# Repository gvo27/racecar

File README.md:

# racecar

This project turns a 1:10 Tamiya TT-02 into a self-driving research platform. It has a two-layer compute stack. A Raspberry Pi 5 does perception, sensor fusion, semantic SLAM and racing-line optimization. An ESP32-S3 does hard-real-time control. This repo holds everything that runs on the car: PWM actuation, failsafes, the host-to-ESP32 protocol, runtime tuning, logging and the Docker/ROS 2 deployment. Setup: [docs/setup.md](docs/setup.md).

## Quick reference

| Task | Commands |
| --- | --- |
| One-time setup (Pi) | `cp .env.example .env`, `make setup`, `make install-host`, `make flash` (ESC off) |
| Start / check / stop | `make car-up`, `make car-ps`, `make car-down` (or `make car-shutdown`) |
| Drive | `make teleop` |
| Sensors | `make viz`, `make rangefinder`, `make lidar-snapshot`, `make lidar-record SECS=30` |
| Tests (no hardware) | `make ros-test`, `make unit`, `make build` |
| Simulation and training | separate repo [racecar-sim](https://github.com/gvo27/racecar-sim). The sim uses the topics in [docs/sensor_contract.md](docs/sensor_contract.md) |
| All targets | `make help` |

**Claude Code plugins.** `.claude/settings.json` lists the project plugins: superpowers, pyright-lsp, clangd-lsp, embedded-skills, ros2-engineering, asd-ste100, claude-md-management, code-simplifier and caveman. Accept the trust prompt, or install each one by hand. Then run `/reload-plugins`:

```bash
claude plugin marketplace add JuliusBrussee/caveman@v4.1.0
claude plugin install <plugin>@<marketplace> --scope project
```

## Compute stack

| Layer | Hardware | Role | Status |
| --- | --- | --- | --- |
| High level | Raspberry Pi 5 | autonomy stack: ROS 2 Jazzy in Docker (`deploy/car/`), supervisor + micro-ROS agent, sends `DriveCmd` (heading, throttle) | phase 2 complete (bench-verified); phase 4 rangefinder + lidar (Slamtec Mapper, `make viz`): compile-only, not bench-verified |
| Real time | ESP32-S3-N16R8 | hardware PWM to servo/ESC, failsafe, telemetry; micro-ROS client over UART0 | this repo, `firmware/esp32/` (env `esp32s3`, micro-ROS) |

## Current inventory

| Component | Item | Documentation |
| --- | --- | --- |
| chassis | Tamiya TT-02 | — |
| battery | 2S 7.4V 80C 5200mAh LiPo Battery Pack | — |
| microcontroller | ESP32 S3 N16R8 | [user guide](https://github.com/microrobotics/ESP32-S3-N16R8/blob/main/ESP32-S3-N16R8_User_Guide.pdf) |
| edge compute | Raspberry Pi 5 | 5V 5A |
| voltage regulator for compute rail | Pololu D36V50F5 (5V 5.5A, 6-50V in) | [pololu.com/product/4091](https://www.pololu.com/product/4091), [archived](docs/datasheets/Pololu%20-%205V%2C%205.5A%20Step-Down%20Voltage%20Regulator%20D36V50F5.htm) |
| rangefinder | Garmin LIDAR-Lite v4 LED, part number 010-02022-00 | [archived PDF](docs/datasheets/LIDAR-Lite%20LED%20v4%20Instructions_EN-US.pdf), [summary](docs/datasheets/rangefinder_lidar_lite_v4.md), [instructions](https://static.garmin.com/pumac/LIDAR-Lite%20LED%20v4%20Instructions_EN-US.pdf) (software name: rangefinder) |
| lidar | Slamtec Mapper M2M1 | [datasheet digest](docs/datasheets/slamtec_mapper_M2M1_datasheet.md) |
| motor controller | THW-1060-BRUSHED | [thw-1060-brushed-esc.md](docs/datasheets/thw-1060-brushed-esc.md) |
| steering servo | DS3225MG | [ds3225_servo.md](docs/datasheets/ds3225_servo.md) |

## Microcontroller Pin map (left header P1 only)

Source of truth: [`firmware/esp32/include/pins.h`](firmware/esp32/include/pins.h). Keep this table identical to it.

```
                ESP32-S3-N16R8   (top view, antenna up)
          P1 (LEFT header)
        ┌─────┬──────────────────────────────┐
  3V3   │  1  │ unused (sensors: own rail)   │
  3V3   │  2  │ unused                       │
  RST   │  3  │ ✗ do not use                 │
  GPIO4 │  4  │ ● STEER_PWM   → servo signal │
  GPIO5 │  5  │ ● THROTTLE_PWM→ ESC signal   │
  GPIO6 │  6  │ ○ BATT_LOW                   │
  GPIO7 │  7  │ ○ IMU_INT                    │
  GPIO15│  8  │ ○ ENC_A                      │
  GPIO16│  9  │ ○ ENC_B                      │
  GPIO17│ 10  │ · spare (UART1 TX)           │
  GPIO18│ 11  │ · spare (UART1 RX)           │
  GPIO8 │ 12  │ ● I2C SDA → rangefinder 3    │
  GPIO3 │ 13  │ ✗ strapping                  │
  GPIO46│ 14  │ ✗ strapping                  │
  GPIO9 │ 15  │ ● I2C SCL → rangefinder 4    │
  GPIO10│ 16  │ · spare                      │
  GPIO11│ 17  │ · spare                      │
  GPIO12│ 18  │ · spare                      │
  GPIO13│ 19  │ · spare                      │
  GPIO14│ 20  │ · spare                      │
  5V    │ 21  │ input only - leave unwired   │
  G     │ 22  │ ■ COMMON GROUND (ESC/servo)  │
        └─────┴──────────────────────────────┘
          [USB] left        [COM] right ← flash / host
   ● active   ○ reserved (no code yet)   · spare   ✗ do not use   ■ ground
```

| P1 # | GPIO | Function | Status |
| --- | --- | --- | --- |
| 4 | 4 | **STEER_PWM** → DS3225 signal | **active** |
| 5 | 5 | **THROTTLE_PWM** → ESC signal | **active** |
| 6 | 6 | *BATT_LOW* (hi/low input) | *reserved* |
| 7 | 7 | *IMU_INT* | *reserved* |
| 8 / 9 | 15 / 16 | *ENC_A / ENC_B* (shaft encoder) | *reserved* |
| 12 / 15 | 8 / 9 | **I2C SDA / SCL** → rangefinder (Garmin pin 3 / 4) | **active** |
| 10, 11, 16-20 | 17, 18, 10, 11, 12-14 | spare | spare |
| 3, 13, 14 | RST, 3, 46 | ~~reset / strapping pins~~ | ~~do not use~~ |
| 22 | G | common ground | power |

Wire colours: signal = yellow/white, power = red, ground = black. Rangefinder I2C: SDA = white, SCL = green. Put a tape flag on the two active signal wires.

## Make commands

This section lists day-to-day commands only, in the order you use them. `make help` lists everything (dev, CI and firmware tools too). [docs/setup.md](docs/setup.md) has the details.

**Once per Pi.** First, run `cp .env.example .env` and add yourself to the `docker` and `dialout` groups (docs/setup.md §1).

| # | Command | What it does |
| --- | --- | --- |
| 1 | `make setup` | Checks git, make and docker. Builds both Docker images (it runs `fw-image` and `ros-image`) |
| 2 | `make install-host` | Needs sudo. Names the ESP32 `/dev/rccar-esp32` and starts the car stack at every boot. Afterwards, unplug the USB cable and plug it in again one time |
| 3 | `make flash` | Switch the ESC off first. Uploads the firmware to the ESP32. Run it again only when `firmware/` changes |

You do not need to run `make config` by hand. `car-up` and the boot service run it.

**Every session**

| # | Command | What it does |
| --- | --- | --- |
| 1 | `make car-up` | Starts the stack (micro-ROS agent, supervisor, lidar driver). After a boot it already runs if you did `install-host`. Running it again is harmless |
| 2 | `make car-ps` | Wait until every service shows `healthy`. Then switch the ESC on |
| 3 | `make teleop` | Drives the car over SSH (arrows, space = brake, `x` = disarm + quit) |
| 4 | `make car-shutdown` | Disarms, stops the stack and offers to power off the Pi. Then switch the ESC off |

**Sensors** (stack running)

| Command | Sensor | What it does |
| --- | --- | --- |
| `make rangefinder` | rangefinder (Garmin LIDAR-Lite v4) | Shows a live distance feed in the terminal |
| `make viz` | lidar (Slamtec Mapper) | Shows scan, map and pose on `localhost:8765` for Foxglove. Forward the port with VS Code SSH |
| `make lidar-imu` | lidar (Slamtec Mapper) | Shows live heading, yaw rate, speed and acceleration. Also saves them to `logs/` |
| `make lidar-snapshot` | lidar (Slamtec Mapper) | Makes one capture to `logs/`: `map.png` (map + scan + pose) and a text summary. Claude Code can read both |
| `make lidar-record SECS=30` | lidar (Slamtec Mapper) | Records the lidar topics to a rosbag (`.mcap`, opens in Foxglove) in `logs/` |
| `make lidar-hw-test` | lidar (Slamtec Mapper) | Automated PASS/FAIL check of the real unit with the car still. Run `make drivers-stop` first and `make car-up` afterwards |

**When needed**

| Situation | Commands |
| --- | --- |
| something looks wrong | `make car-logs` |
| USB cable replugged | `make car-down`, then `make car-up` |
| first drive, or the servo/linkage changed | `make calibrate`, then `make test` (steering sweep; the motor never runs) |
| edited `tuning.toml` | `make tune` |
| after `git pull` | `make car-down`, `make ros-image`, `make flash` (only if `firmware/` changed, ESC off), `make car-up` |

## Wiring: Rangefinder (Garmin LIDAR-Lite v4 LED)

The software name is *rangefinder*. Datasheet: [archived PDF](docs/datasheets/LIDAR-Lite%20LED%20v4%20Instructions_EN-US.pdf), [summary](docs/datasheets/rangefinder_lidar_lite_v4.md). Power off while wiring.

| Garmin pin | Name | Wire | Connect to |
| --- | --- | --- | --- |
| 1 | VIN (5 V, 4.75-5.25 V) | red | regulated 5 V **sensor rail** (never ESP32 5V/3V3) |
| 2 | GND | black | common ground (P1-22) |
| 3 | I2C SDA | **white** | GPIO8 (P1-12) |
| 4 | I2C SCL | **green** | GPIO9 (P1-15) |
| 5-10 | GPIOA, GPIOB, nRF debug | n/a | leave unconnected |

## Power rules

1. **The ESP32 powers nothing.** It outputs only actuator signals and communications. A separate regulated power rail powers the sensors. This rail shares ground with the ESP32. All signals stay at ≤ 3.3 V.
2. Servo power comes from the built-in 6 V / 3 A BEC of the ESC (red wire of the throttle lead). Connect it with a Y-harness.
3. Connect the grounds of the ESP32, ESC and servo (P1-22).

## Power-up sequence

1. ESC **off**. Wheels off the ground.
2. Connect the USB cable to **COM**. The ESP32 boots and sends neutral (1500 µs) on both channels. Then run `make car-up`.
3. ESC **on**. It beeps and learns neutral.
4. To power down, do the steps in reverse order. Switch the ESC off first. **Always switch the ESC off before `make flash`.**

## Repo layout

```
rccar_msgs/        interface contract: DriveCmd, Telemetry, McuEvent, SupervisorState, McuCommand, Reset, ...
rccar_supervisor/  safety authority: arbitration, latched stop, sole publisher of /rccar/mcu/drive
rccar_mcu_bridge/  lifecycle node: typed services over McuCommand, tuning push, FIRMWARE_KEYS
rccar_teleop/      admin keyboard teleop (SSH)
rccar_calibration/ calibrate, bench_test, tune
rccar_bringup/     launch (car.launch.py), tuning.toml -> ROS parameters
firmware/esp32/    ESP32 firmware (PlatformIO): src/main.cpp, include/pins.h, extra_packages/rccar_msgs (synced copy), rccar.meta
deploy/car/        compose.yaml, 99-rccar.rules (udev), rccar.service (systemd); deploy/render_env.py (make config)
docker/            firmware.Dockerfile, ros.Dockerfile (+ entrypoint.sh, ros-test.sh)
models/            manifest.yaml (weights are not in git), cache/ gitignored
repos/             rccar.repos (third-party ROS sources, vcstool)
tuning.toml        all runtime tuning + [platform.*]; pushed to the ESP32 by mcu_bridge
.env.example       template for the gitignored .env
logs/              session history (*.jsonl, gitignored)
docs/              setup.md, docker_ros_plan.md, proposal, datasheets/
.claude/           CLAUDE.md, layout.yaml, rules/, agents/
.github/           workflows/{firmware,ros}.yml
Makefile           every command (make help)
```

Bench checklist (the procedure that verified phase 2): [docs/setup.md](docs/setup.md#phase-2-bench-checklist-user-run). Roadmap: [docs/docker_ros_plan.md](docs/docker_ros_plan.md). Firmware design: [docs/esp32-firmware-proposal.md](docs/esp32-firmware-proposal.md).

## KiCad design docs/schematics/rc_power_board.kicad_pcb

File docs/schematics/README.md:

# Power distribution board (baseline schematic)

Draft KiCad project for the car's power board. A 2S LiPo comes in; the board puts out `VBAT`, `+5V_CPU`, `+5V_SENS` and `+3V3_SENS` on a common `GND`, and routes `+6V_BEC` from the ESC to the servo. The ESC's own battery power is off-board. This is a **review draft**: every value marked `TBD` is unconfirmed (project rule: no unconfirmed parameters).

| File | What it is |
| --- | --- |
| `design_overview.md` | The design meeting summary: one short entry per feature, the power budget and the decisions wanted. |
| `bom.md` | How the BOM is made (`make bom`, symbol fields), fuse notes, stock notes. |
| `bom.csv` | BOM exported from the schematic fields by `make bom` (generated; commit it). |
| `bom_offboard.csv` | Hand-kept BOM of parts with no symbol (XH housings, crimps, stock, J6/J7 options). |
| `fab_handoff.md` | Rev A CNC-milling handoff (Makera Carvera) plus later-revision fab checklist: DRC/net classes, rivets, holes, IPC-2221 table, connector table, export, sign-off. |
| `power_board_plan.md` | The build guide and background: rails, power budget, trace widths, a step-by-step KiCad guide and open questions. Exported from the live doc linked at its top. |
| `power_architecture.png` | Block diagram used by the plan. |
| `rc_power_board.kicad_pro` / `.kicad_sch` | KiCad project and the one-sheet A3 schematic (regions A to E plus notes). |
| `rc_power.kicad_sym` + `sym-lib-table` | Project symbol library: `D36V50F5` (all 12 module pins, used by U1 and U2), `REG_MODULE` (generic VIN/GND/VOUT/EN, no longer used on the board) and one power symbol per rail. |
| `rc_power_board.kicad_pcb` / `.kicad_dru` | Rev A board, routed, for review only (no Gerber or CAM files). The `.kicad_dru` holds rule `U3_fine`. |
| `rc_power.pretty/` + `fp-lib-table` | Project footprint library: `Pololu_D36V50Fx` (U1 and U2: 12 pads and the full 25.4 x 25.4 mm body, from Pololu's drawing; facts in `docs/datasheets/regulator_pololu_d36v50f5.md`). |
| `milling.toml`, `milling_waivers.toml` | Milling limits (each value `assumed` or `confirmed`) and the waiver list for the milling check. |
| `tools/` | Python tools and tests that run in the KiCad image: `build_pcb.py`, `placement.py`, `route_pcb.py`, `check_board.py`, `milling_check.py`, `review_plots.py`. |
| `review/` | Review package: DRC report, milling check, layer PDF, 1:1 PDF, `README.md`. |
| `rc_power_board.pdf` | Plot of the sheet, for review without KiCad. |
| `.kicad-happy.json` | Config for the kicad-happy Claude plugin (analysis output in `analysis/`, gitignored except the manifest). |

## KiCad version

The project version is **KiCad 10.0**; KiCad 9 or older cannot open a KiCad 10 save.

The committed `.kicad_sch` is now KiCad 10 format: `kicad-cli sch upgrade` (10.0.8) saved it with the U2 footprint change. The owner's GUI steps stay open: Update Symbols from Library (the 3 `lib_symbol_mismatch` warnings, D2 to D4), a re-plot of the PDF, and the owner's KiCad 10 ERC.

The single-fuse revision is regenerated in KiCad 7 format again. Owner steps: close KiCad, pull, open, Update Symbols from Library, save, run ERC, re-plot the PDF, push.

Previous revision: the meeting-cleanup revision was generated in KiCad 7 format, then opened, symbol-updated (D2–D4) and saved in KiCad 10.0 by the owner (94ccd72), with label positions tidied in dd946f3. Edit the KiCad 10 files from here on; close KiCad before pulling. `rc_power_board.kicad_pro` (net classes, ERC severities) is the owner's KiCad 10 file.

## U1 and U2 = Pololu D36V50F5 (current revision)

- **U1 and U2** are both the Pololu D36V50F5 (#4091, 5 V, 5.5 A typical). Owner decision 2026-11-12: the owner has two modules, and the same part on both rails gives a swap spare. This replaces the D24V90F5 assumption for U2 (2026-11-11).
- Facts, archived drawing and graphs: `docs/datasheets/regulator_pololu_d36v50f5.md`. The D24V90F5 note stays as history (`regulator_pololu_d24v90f5.md`, superseded).
- Both modules use the symbol `rc_power:D36V50F5` and the footprint `rc_power:Pololu_D36V50Fx`. The footprint shows the real 25.4 x 25.4 mm body (the first rev A layout used a plain pin header and put the body over J6 and J7). U2 EN, VRP and PG have no-connect flags, as U1 EN and VRP.
- **Flag:** dropout is about 1.0 V at 5 A (Pololu graph). Near the 6.0 V cutoff the +5V_SENS output can fall below 5 V, and the Mapper needs at least 4.8 V. Bench check at J11 during Mapper startup.
- Decisions on 2026-11-11 (owner): no reverse-polarity protection on rev A (the modules have their own); U3 keeps the stock SOT-23-5 footprint with the `U3_fine` DRC rule.
- Plan: `docs/plans/2026-11-11-power-board-pcb-rev-a.md` (Task 7c).

## Rev A PCB (review only)

The board is built and routed headless in the pinned KiCad 10.0.8 image: `make kicad-image`, then `make erc pcb-build pcb-route pcb-check pcb-mill-check pcb-review pcb-test`. Freerouting 2.5.0 (pinned by digest) routes it. `pcb-build` refuses to overwrite an existing board without `--force`: after the first build the `.kicad_pcb` is the owner's file. Results, assumptions and the owner's GUI checks are in `review/README.md`. Gerber, drill and CAM export wait for the lab tech.

## ATO fuse, JST-XH convention, Garmin I2C (earlier revision)

- **F1** is a standard ATO/ATC blade fuse in a Littelfuse FLR 178.6165.0001 holder (`Fuse:FuseHolder_Blade_ATO_Littelfuse_FLR_178.6165`); value `TBD ATO/ATC blade 15A` (15 A decided by the Mapper load, see the Mapper revision below). Proposed fuse: Littelfuse 0257015.PXPV (15 A). Details in `bom.md`.
- **JST-XH (2.5 mm) is the connector convention** for sensors and low-power parts (single Dupont jumper sockets push onto the XH pins for breadboard debugging; 2.54 mm multi-pin housings do not fit; parts in lab stock). Exceptions: J1 (battery T-plug pads), J6/J7 (USB-C pigtail screw terminals, over 3 A).
- **J3, J4:** 3-pin XH, pins 1 GND, 2 +6V_BEC, 3 signal (follows the ESC/servo lead; XH 2.50 mm does not mate with stock 2.54 mm plugs: re-terminate only 22 AWG leads, else an adapter lead). **J5:** 6-pin XH: 1 `U1_PG` (GPIO TBD), 2 `THROTTLE_PWM` GPIO5, 3 `STEER_PWM` GPIO4, 4 `I2C_SDA` GPIO8, 5 `I2C_SCL` GPIO9, 6 GND. **J8:** Garmin LIDAR-Lite v4, 4-pin XH, pin order = Garmin 1-4 (+5V_SENS, GND, SDA, SCL); no external I2C pull-ups. J9, J11-J14 stay 2-pin XH (1 V+, 2 GND); J11 now hosts the Slamtec Mapper (see below). Pin order convention and crimp table: `fab_handoff.md`.
- **Netlist then: 39 parts, 21 nets** (adds `I2C_SDA`, `I2C_SCL`); now 40 parts, 21 nets (see the Mapper revision).
- **Power5A** track width is 1.6 mm (now also `+5V_SENS`, see below). Computed IPC-2221 widths are in `fab_handoff.md` (2 oz stock).
- **Owner steps:** close KiCad, pull, open, Update Symbols from Library, save in KiCad 10, run ERC, Assign Footprints check (XH and ATO footprints), re-plot the PDF, push.

## Slamtec Mapper on `+5V_SENS` (earlier revision)

- **J11** (was `Spare 5V`) now hosts the Slamtec Mapper M2M1 lidar. Harness: J11 2-pin XH, XHP-2 housing, 22 AWG 3 A USB-A male 2-wire pigtail (pin 1 `+5V_SENS` to red/VBUS, pin 2 GND to black). Mapper supply 4.8 V min / 5 V typ / 12 V max; running 0.75 A typ, 1.3 A max; startup 1.4-1.6 A for a few seconds; ripple 20 mV typ, 50 mV max (from its datasheet on branch `lidar`). Not powered from Pi USB or straight from the pack.
- **C9** (`Device:C_Polarized`, `TBD >=100uF low-ESR >=10V`, footprint `CP_Radial_D8.0mm_P3.50mm`) added on `+5V_SENS` / GND at J11 for the startup surge and ripple.
- **Budget (computed):** `+5V_SENS` 3.3 A -> 4.6 A worst case running, 4.9 A at Mapper startup. U2 must now be >= 6 A: the Pololu D36V50F5 (owner 2026-11-12) gives about 7.4 A at 6 V in and about 8 A at 8.4 V in (Pololu graph); dropout near the 6.0 V cutoff is a bench check. U2 input 3.99 A at 6.4 V, 4.26 A at 6.0 V; U1 input 4.43 A / 4.72 A. Board `VBAT` load about 8.4 A at 6.4 V, 9.0 A at 6.0 V, about 9.3 A briefly at startup (was 7.3 / 7.8 A).
- **F1 = 15 A** (10 A would run at 84-93 % of rating, over the ~75 % rule; 15 A gives 56-62 %). Copper stays sized for 16.5 A. Inrush margin unchanged.
- **Net classes:** `+5V_SENS` moved from Power3A (1.0 mm) to Power5A (1.6 mm) in `rc_power_board.kicad_pro` (about 4.9 A; IPC-2221 5.0 A row, 2 oz: 1.4 mm at ΔT 10 C). `*+6V_BEC` stays Power3A.
- **DRC rules** in `rc_power_board.kicad_pro` (board.design_settings.rules) set to match the CNC docs: `min_clearance` 0.4, `min_track_width` 0.5, `min_via_diameter` 2.0, `min_via_annular_width` 0.45, `min_through_hole_diameter` 0.8 (C9 drill; methods TBD).
- **Schematic:** J3 and its wires/symbols sit 1.27 mm up-left of the generator's old position, ported from the owner's 53ac275 save. Netlist: 40 parts, 21 nets; everything but C9 is identical to the previous revision. Notes box updated (budget, F1, U2, `+5V_SENS` class, new note 14 for the Mapper).
- **Owner steps:** open in KiCad 10, Update Symbols, save, run ERC, re-plot; choose C9 and U2 parts.

## CNC-milled prototype (Makera Carvera)

Rev A is milled in-house from Kepro P22-465G 2 oz double-sided FR-4 (4" x 6", 152.4 x 101.6 mm; lab template, `example/README.md`); no fab house, no plated holes, vias are soldered copper rivets.

- **Rivets (update):** lab stock is an LPKF EasyContac kit (0.6/0.8/1.0/1.2 mm, with setting tool). Default via = 0.8 mm rivet, drill 1.1 mm, pad 2.0 mm (matches the existing `.kicad_pro` via settings); 1.2 mm optional for high current. Table and source: `fab_handoff.md`. BOM rivets now $0.

- **`rc_power_board.kicad_pro`:** all four net classes clearance 0.2 -> 0.4 mm; Default track 0.25 -> 0.5 mm; via diameter/drill for all classes -> 2.0 / 1.1 mm (LPKF EasyContac 0.8 mm rivet). DRC rules set: clearance 0.4, track 0.5, via 2.0/1.1, annular 0.45, min hole 0.8; plan's net-class table updated.
- **Docs:** `fab_handoff.md` restructured (A: CNC prototype, B: fab house later) with a JST header table for every external connection; `bom.md` adds stock, rivets, dowels, bits and optional VH/XH rows, no PCB fab cost (total about 87.0 USD, about 47.1 excluding U1 after the rivet update); `design_overview.md` and `.claude/rules/schematics.md` updated.
- **Owner steps:** pull; open Board Setup in KiCad 10 and verify the preloaded design-rule minimums (clearance 0.4, track 0.5, via 2.0, annular 0.45, min hole 0.8); the net-class values are provisional; confirm the bit list (incl. a 1.1 mm bit) with the lab tech; decide the U3 footprint option. (The DRC minimums are now set in `rc_power_board.kicad_pro`, see the Mapper revision; the Mapper question is decided.)

## Meeting-cleanup revision (what changed)

- **Wiring for traceability.** Each region's local nets (`VBAT_RAW`, `LDO_IN`, the rail outputs; `VIN_CPU`/`VIN_SENS` were merged into `VBAT`, see below) run as one bus from source to load, with no crossings. Each bus carries a single net label so the net keeps its name. GND is still drawn as symbols.
- **ESC power is off-board.** The battery feeds the ESC directly on its own 12 AWG leads, carrying up to 20 A of motor current. J2, F2 and `VBAT_ESC` are removed. On the board, the ESC is now only the J3 3-wire receiver lead: throttle PWM plus the 6 V BEC. Board load on `VBAT` was then about 7.3 A worst case (about 7.8 A at the 6.0 V cutoff; now 8.4 / 9.0 A with the Mapper, F1 = 15 A). A note on the sheet records the ESC draw.
- **U1 EN is left unconnected (feature archived).** The module's internal pull-up keeps U1 always on. Q1, R4, `ESP_SHDN` and region F are removed. U1 PG still goes to the ESP32.
- **The radar header (J10) is removed.** The gap in reference numbers is deliberate, so J11 keeps its name.
- **`+6V_BEC`** now uses a project rail symbol, like the other rails.
- **J5** was 4-pin in this revision (now 6-pin, see the current revision): 1 `U1_PG`, 2 `THROTTLE_PWM` (GPIO5), 3 `STEER_PWM` (GPIO4), 4 GND. The `U1_PG` GPIO is TBD until firmware adds it; when it does, update `pins.h` and the README pin table together.

## Single-fuse revision (what changed)

- **One replaceable main fuse, F1, for the whole board** (compute and both sensor rails), because the fuse inventory is high-current. Branch fuses F3 (compute) and F4 (sensor) are removed.
- **Nets `VIN_CPU` and `VIN_SENS` are gone**, merged into `VBAT` (class HighCurrent). U1 VIN and U2 VIN sit directly on `VBAT`.
- **F1** was a Mini (ATM) blade fuse in a Keystone 3568 holder (superseded by the ATO/ATC revision above). Rating discussion is in `bom.md`.
- **Trade-off:** a sensor-branch short now opens F1 and drops compute too. U1 and U2 have their own output current limiting.
- **Netlist then: 39 parts, 19 nets (now 40 parts, 21 nets, see the Mapper revision).** Net classes then: HighCurrent = `*VBAT*`, GND; Power5A = `+5V_CPU`; Power3A = `+5V_SENS`, `*+6V_BEC` (now `+5V_SENS` is Power5A).
- **U1 EN** stays unconnected until the rev 2 prototype board. U1 is in hand; U2 is not bought yet.
- **New docs:** `bom.md` and `fab_handoff.md`.

## Design notes

- **Rail symbols.** Each rail is a project power symbol whose hidden pin name and Value both equal the rail name, instead of a renamed `power:VCC`. This keeps nets correct in KiCad 7 (where the pin name sets the net) and in 8 and later (where the Value does).
- **U1, Pololu D36V50F5.**
  - Drawn with all 12 pins: 1 PG, 2 EN, 3–4 VRP, 5–6 VIN, 7–10 GND, 11–12 VOUT.
  - Footprint `PinHeader_2x06_P2.54mm_Vertical`. Check the pin numbering against Pololu's dimension drawing before layout.
  - Each header pin is rated 3 A, so VIN, VOUT and GND use their pin pairs.
  - VRP is unused: the sensor buck is fed from `VBAT` (VRP would overload U1's 6 A VIN pin pair).
  - Rated 5.0 V / 5.5 A, against the plan's 5.1 V / ≥ 6 A target.
- **J1** is a pair of wire pads for the battery's T-plug pigtail (12 AWG). The pad footprint is a placeholder; size TBD.
- **J6/J7** are 2-wire USB-C pigtails into the Pi 5 and the ESP32's left USB-C port, so each board's own USB-C input protection stays in the path. They are 20 AWG, 30 cm long, and drop about 0.10 V at 5 A; trim them to 10–15 cm.
- **PWR_FLAG** symbols are ERC-only markers. They tell ERC that power enters a net that is fed through a fuse or ferrite. They have no physical part and are not on the PCB. The probe points are TP1–TP3.
- **LED resistors** connect pin-to-pin to their LEDs, so those three nets carry KiCad's auto names (`Net-(D2-A)` and so on).
- **Net-class patterns** are `*VBAT*`, `+5V_CPU`, `+5V_SENS` and `*+6V_BEC`. The leading `*` matches the `/` that KiCad puts in front of local-label nets.
- **D1** is `Device:D_Zener`, used as a unidirectional TVS, cathode to `VBAT`.
- **Placeholder footprints.** All ratings are TBD; pick real parts before layout.
  - F1: `Fuse:FuseHolder_Blade_ATO_Littelfuse_FLR_178.6165` (ATO/ATC blade).
  - C1: 10 mm radial electrolytic.
  - D1: SMB.
  - FB1: 0805.
  - TP1–TP3: 1.5 mm pads.
  - U2: module TBD, no footprint yet.

## Verification so far

The current revision (Mapper on J11): **40 parts, 21 nets**, per the regenerated netlist (KiCad 7.0.11 `kicad-cli`); the only netlist change vs the previous revision is C9 added to `+5V_SENS` / GND. The kicad-happy analyzer finds 40 parts, 21 nets, 4 no-connects and the same findings as before. The owner's KiCad 10 ERC on this revision is pending (the previous save, 53ac275, was clean). The figures below are from the earlier (41 parts, 21 nets) revision.

The previous revision was checked with KiCad 7.0.11 `kicad-cli`, the kicad-happy analyzer and the owner's KiCad 10 ERC:

- **Netlist: 41 parts, 21 nets.** The only single-pin nets are U1 EN, U1 VRP ×2, U2 EN and U3 NC. All of them are intentionally unconnected and carry no-connect flags.
- **Analyzer:** finds the same 41 parts and 21 nets. U1 and U2 are classified as switching regulators, U3 as a 3.3 V LDO, and D2–D4 as resistor-limited LEDs. The remaining findings are expected for a draft:
  - no MPNs or datasheets (all TBD);
  - no footprint for U2;
  - "missing pull-up" on U1 PG (the ESP32's internal pull-up handles it);
  - "missing pull-up" on U3 EN (it is tied to VIN, per the AP2112 datasheet).
- **PDF:** rendered and visually checked: no wire crossings in any region, and no text overlaps.
- **ERC in KiCad 10 (owner-run, 94ccd72): clean**, after Update Symbols from Library. `rc_power_board.pdf` re-plotted from KiCad 10 (dd946f3).
- **Analyzer on the KiCad 10 save (dd946f3):** still 41 parts, 21 nets, 4 no-connects, so the upgrade and label tidy changed no connections.
- **Not yet done:** SPICE, PCB layout.

## Working on this folder with Claude Code

The repo enables the kicad-happy plugin (`.claude/settings.json`). Rules for this folder are in `.claude/rules/schematics.md`. Typical asks are "review docs/schematics", "check the power budget against the schematic" and "simulate the subcircuits". SPICE needs `ngspice` installed on the host.

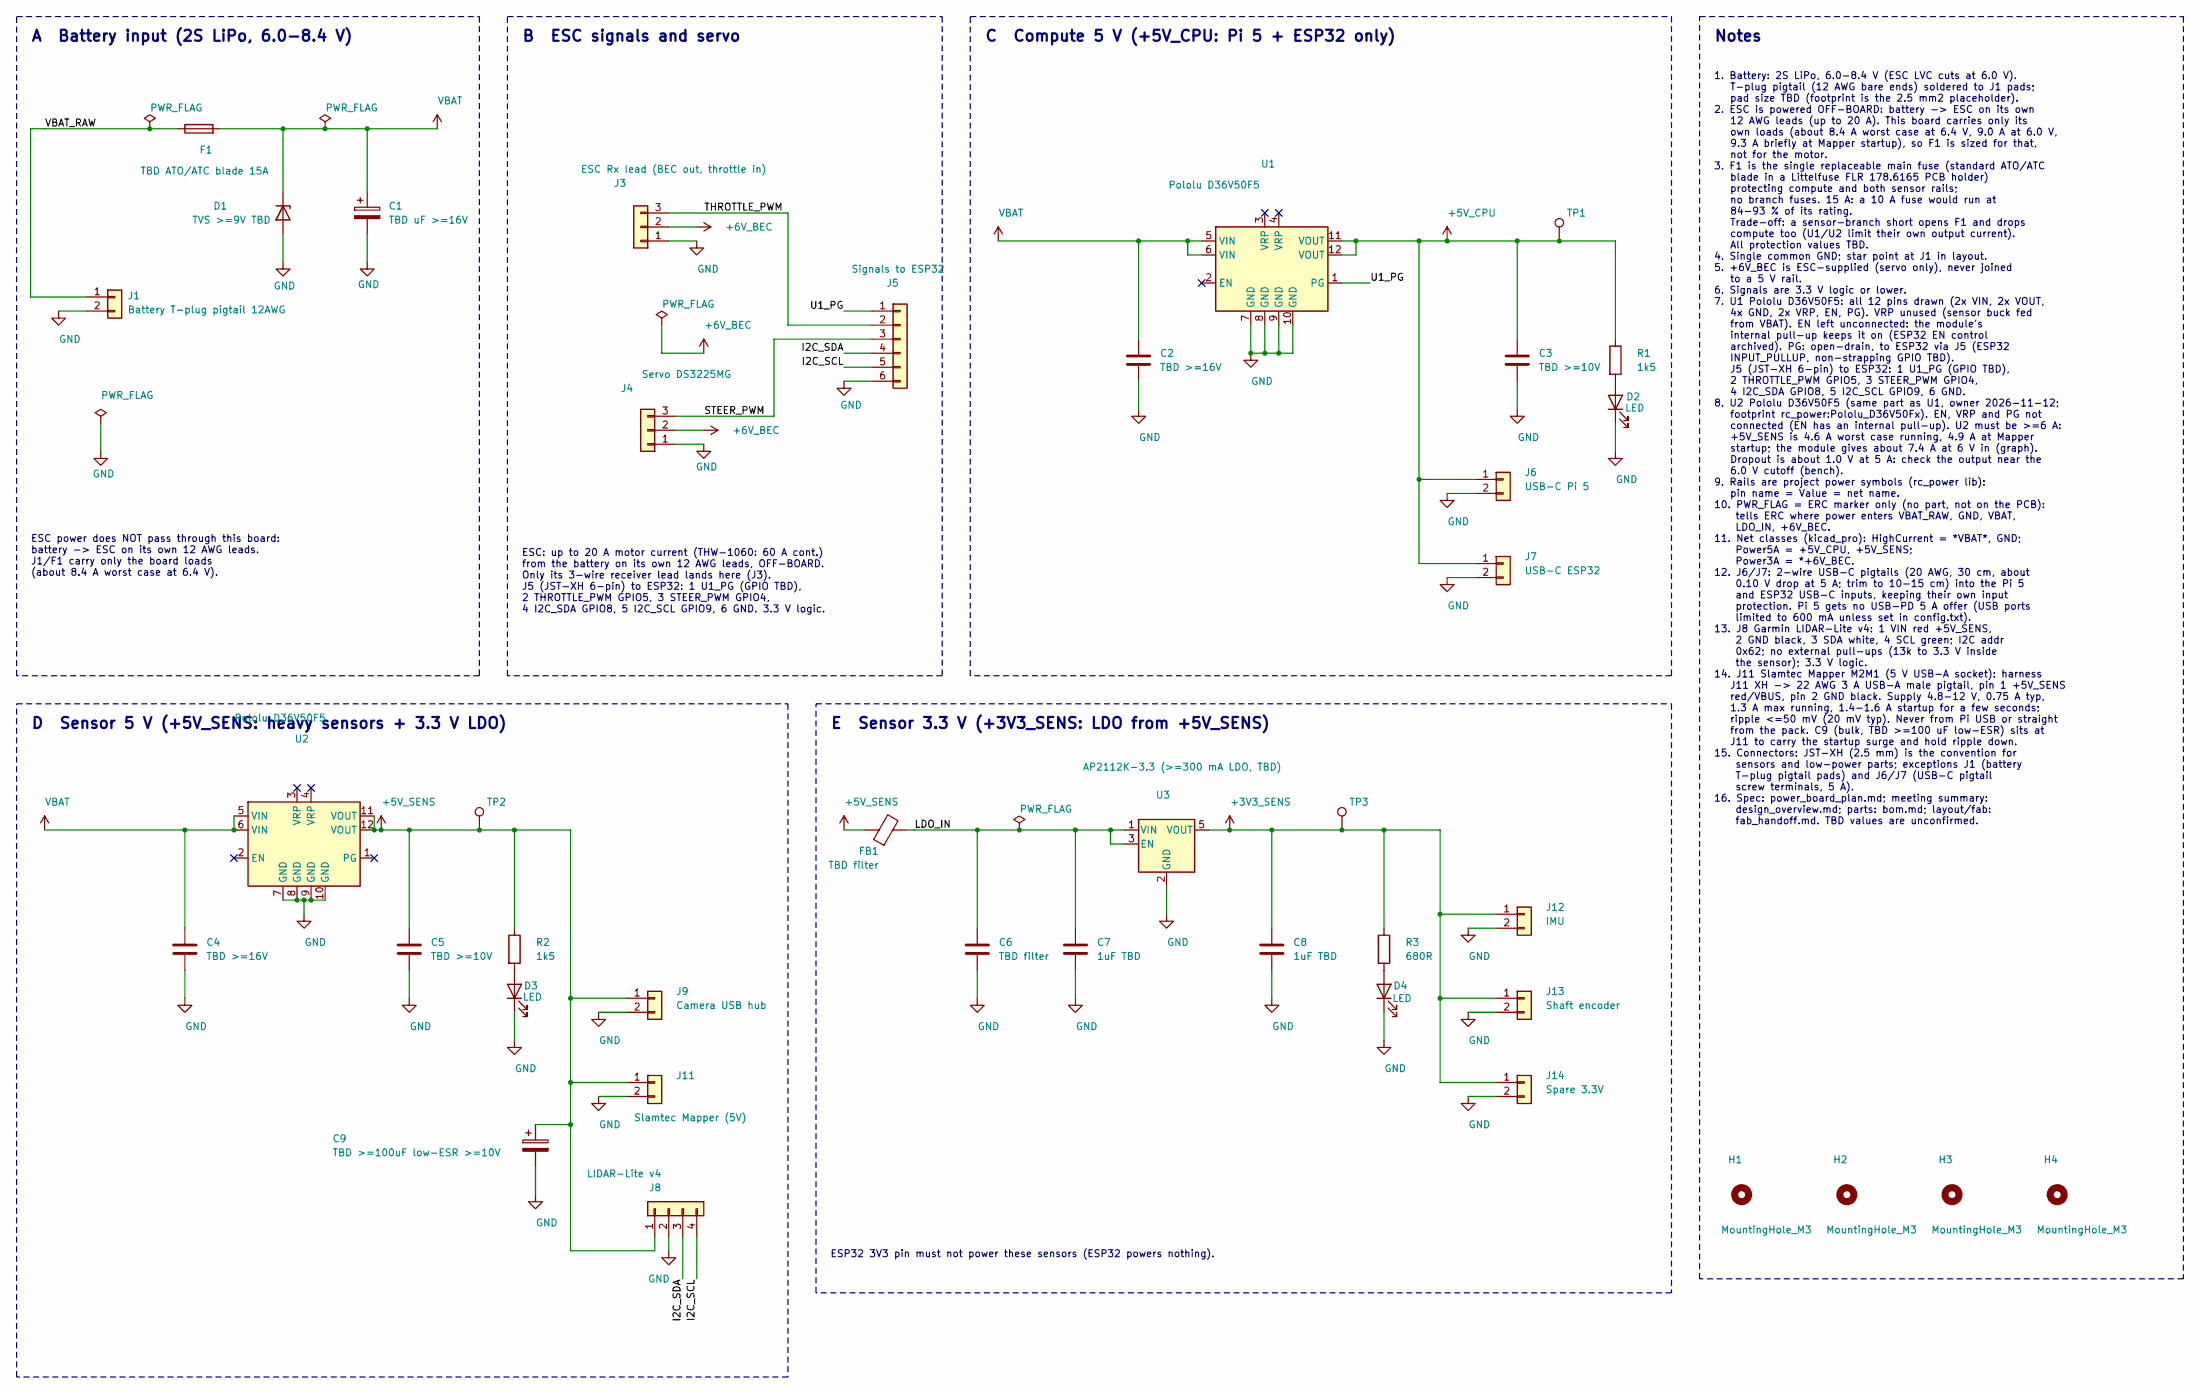
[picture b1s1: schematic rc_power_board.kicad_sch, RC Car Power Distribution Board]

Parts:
C1: TBD uF >=16V; CP_Radial_D10.0mm_P5.00mm; MPN EEU-FR1E471
C2, C4: TBD >=16V; C_0805_2012Metric; MPN CC0805KRX5R8BB106
C3, C5: TBD >=10V; C_0805_2012Metric; MPN GRM21BR61A226ME44L
C6: TBD filter; C_0805_2012Metric; MPN CC0805KRX5R8BB106
C7, C8: 1uF TBD; C_0805_2012Metric; MPN CL21B105KBFNNNE
C9: TBD >=100uF low-ESR >=10V; CP_Radial_D8.0mm_P3.50mm; MPN TBD
D1: TVS >=9V TBD; D_SMB; MPN SMBJ10A
D2, D3, D4: LED; LED_0805_2012Metric; MPN LTST-C171GKT
F1: TBD ATO/ATC blade 15A; FuseHolder_Blade_ATO_Littelfuse_FLR_178.6165; MPN Littelfuse 0257015.PXPV (ATO 257, 15 A,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
FB1: TBD filter; L_0805_2012Metric; MPN BLM21PG221SN1D
H1, H2, H3, H4: MountingHole_M3; MountingHole_3.2mm_M3; MPN none
J1: Battery T-plug pigtail 12AWG; SolderWire-2.5sqmm_1x02_P8.8mm_D2.4mm_OD4.4mm; MPN none
J3: ESC Rx lead (BEC out, throttle in); JST_XH_B3B-XH-A_1x03_P2.50mm_Vertical; MPN B3B-XH-A(LF)(SN)
J4: Servo DS3225MG; JST_XH_B3B-XH-A_1x03_P2.50mm_Vertical; MPN B3B-XH-A(LF)(SN)
J5: Signals to ESP32; JST_XH_B6B-XH-A_1x06_P2.50mm_Vertical; MPN B6B-XH-A(LF)(SN)
J6: USB-C Pi 5; TerminalBlock_Phoenix_MKDS-1,5-2-5.08_1x02_P5.08mm_Horizont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; MPN 1715721
J7: USB-C ESP32; TerminalBlock_Phoenix_MKDS-1,5-2-5.08_1x02_P5.08mm_Horizont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; MPN 1715721
J8: LIDAR-Lite v4; JST_XH_B4B-XH-A_1x04_P2.50mm_Vertical; MPN B4B-XH-A(LF)(SN)
J9: Camera USB hub; JST_XH_B2B-XH-A_1x02_P2.50mm_Vertical; MPN B2B-XH-A(LF)(SN)
J11: Slamtec Mapper (5V); JST_XH_B2B-XH-A_1x02_P2.50mm_Vertical; MPN B2B-XH-A(LF)(SN)
J12: IMU; JST_XH_B2B-XH-A_1x02_P2.50mm_Vertical; MPN B2B-XH-A(LF)(SN)
J13: Shaft encoder; JST_XH_B2B-XH-A_1x02_P2.50mm_Vertical; MPN B2B-XH-A(LF)(SN)
J14: Spare 3.3V; JST_XH_B2B-XH-A_1x02_P2.50mm_Vertical; MPN B2B-XH-A(LF)(SN)
R1, R2: 1k5; R_0805_2012Metric; MPN RC0805FR-071K5L
R3: 680R; R_0805_2012Metric; MPN RC0805FR-07680RL
TP1: +5V_CPU; TestPoint_Pad_D1.5mm; MPN none
TP2: +5V_SENS; TestPoint_Pad_D1.5mm; MPN none
TP3: +3V3_SENS; TestPoint_Pad_D1.5mm; MPN none
U1, U2: Pololu D36V50F5; Pololu_D36V50Fx; MPN Pololu D36V50F5
U3: AP2112K-3.3 (>=300 mA LDO, TBD); SOT-23-5; MPN AP2112K-3.3TRG1

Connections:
+3V3_SENS: C8.1, J12.1, J13.1, J14.1, R3.1, TP3.1, U3.5 (VOUT)
+5V_CPU: C3.1, J6.1, J7.1, R1.1, TP1.1, U1.11 (VOUT), U1.12 (VOUT)
+5V_SENS: C5.1, C9.1, FB1.1, J8.1, J9.1, J11.1, R2.1, TP2.1, U2.11 (VOUT), U2.12 (VOUT)
+6V_BEC: J3.2, J4.2
/I2C_SCL: J5.5, J8.4
/I2C_SDA: J5.4, J8.3
/LDO_IN: C6.1, C7.1, FB1.2, U3.1 (VIN), U3.3 (EN)
/STEER_PWM: J4.3, J5.3
/THROTTLE_PWM: J3.3, J5.2
/U1_PG: J5.1, U1.1 (PG)
/VBAT_RAW: F1.1, J1.1
GND: C1.2, C2.2, C3.2, C4.2, C5.2, C6.2, C7.2, C8.2, C9.2, D1.2 (A), D2.1 (K), D3.1 (K), D4.1 (K), J1.2, J3.1, J4.1, J5.6, J6.2, J7.2, J8.2, J9.2, J11.2, J12.2, J13.2, J14.2, U1.7 (GND), U1.8 (GND), U1.9 (GND), U1.10 (GND), U2.7 (GND), U2.8 (GND), U2.9 (GND), U2.10 (GND), U3.2 (GND)
unnamed: D2.2 (A), R1.2
unnamed: D3.2 (A), R2.2
unnamed: D4.2 (A), R3.2
VBAT: C1.1, C2.1, C4.1, D1.1 (K), F1.2, U1.5 (VIN), U1.6 (VIN), U2.5 (VIN), U2.6 (VIN)

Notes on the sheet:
B ESC signals and servo
C Compute 5 V (+5V_CPU: Pi 5 + ESP32 only)
ESP32 3V3 pin must not power these sensors (ESP32 powers nothing).
ESC power does NOT pass through this board: battery -> ESC on its own 12 AWG leads. J1/F1 carry only the board loads (about 8.4 A worst case at 6.4 V).
ESC: up to 20 A motor current (THW-1060: 60 A cont.) from the battery on its own 12 AWG leads, OFF-BOARD. Only its 3-wire receiver lead lands here (J3). J5 (JST-XH 6-pin) to ESP32: 1 U1_PG (GPIO TBD), 2 THROTTLE_PWM GPIO5, 3 STEER_PWM GPIO4, 4 I2C_SDA GPIO8, 5 I2C_SCL GPIO9, 6 GND. 3.3 V logic.
D Sensor 5 V (+5V_SENS: heavy sensors + 3.3 V LDO)
A Battery input (2S LiPo, 6.0-8.4 V)
1. Battery: 2S LiPo, 6.0-8.4 V (ESC LVC cuts at 6.0 V). T-plug pigtail (12 AWG bare ends) soldered to J1 pads; pad size TBD (footprint is the 2.5 mm2 placeholder). 2. ESC is powered OFF-BOARD: battery -> ESC on its own 12 AWG leads (up to 20 A). This board carries only its own loads (about 8.4 A wo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
E Sensor 3.3 V (+3V3_SENS: LDO from +5V_SENS)
Notes

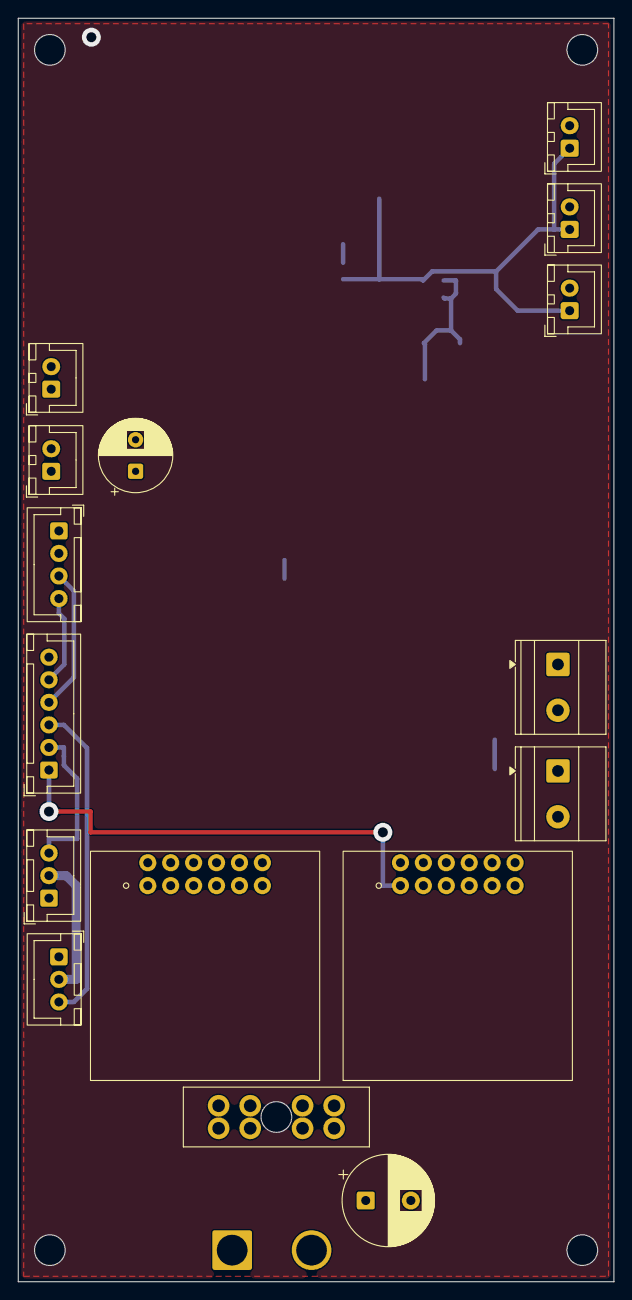
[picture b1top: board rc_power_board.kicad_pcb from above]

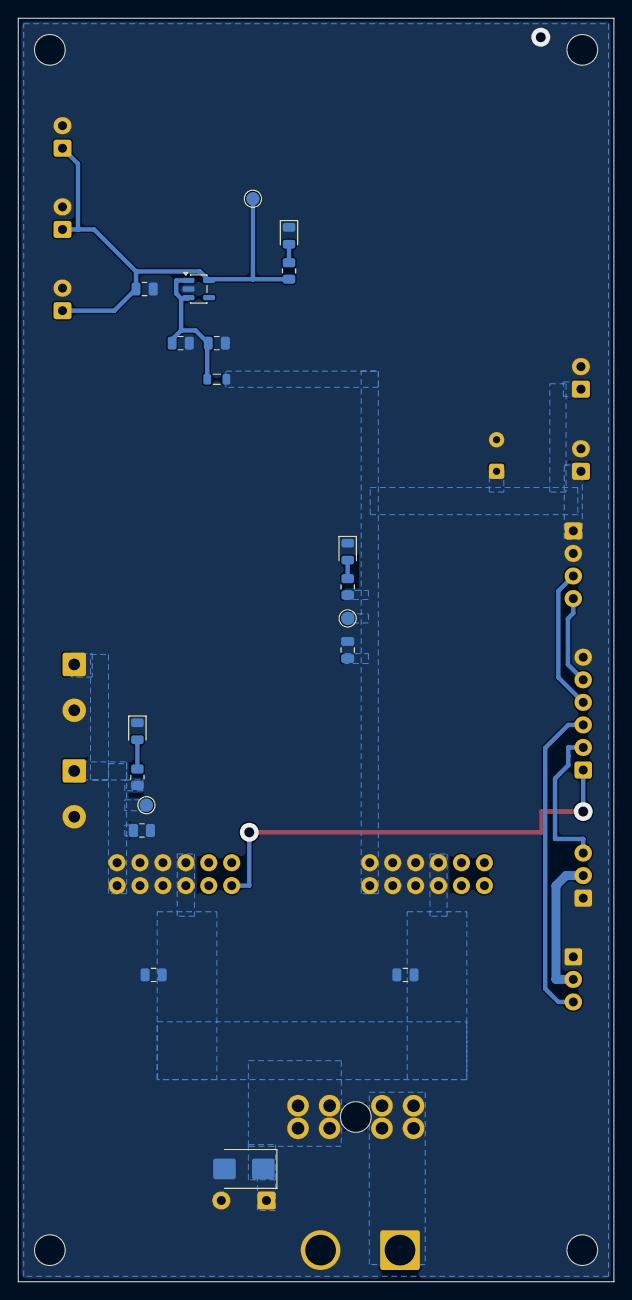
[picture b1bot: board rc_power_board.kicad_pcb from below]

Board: 2 copper layers, 66.0 x 140.0 mm, 40 parts (19 on the bottom side), 16 nets.

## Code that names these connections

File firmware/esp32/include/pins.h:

#pragma once
// Pin map for ESP32-S3-N16R8 -- LEFT header (P1) only, see README.md.
// P1 order (USB ports at the bottom, chip facing you):
//   3V3 3V3 RST 4 5 6 7 15 16 17 18 8 3 46 9 10 11 12 13 14 5V G

// ---- Active (driven by this firmware) ----
constexpr int PIN_STEER_PWM    = 4;   // P1-4  -> DS3225 servo signal
constexpr int PIN_THROTTLE_PWM = 5;   // P1-5  -> THW-1060 ESC throttle signal
constexpr int PIN_I2C_SDA      = 8;   // P1-12 rangefinder pin 3 SDA; bus shared with IMU later
constexpr int PIN_I2C_SCL      = 9;   // P1-15 rangefinder pin 4 SCL; bus shared with IMU later

// ---- Reserved for future devices (NOT configured by this firmware) ----
constexpr int PIN_BATT_LOW     = 6;   // P1-6  battery hi/low digital in (ADC1_CH5 capable)
constexpr int PIN_IMU_INT      = 7;   // P1-7  6-axis IMU interrupt / data-ready
constexpr int PIN_ENC_A        = 15;  // P1-8  shaft encoder channel A (PCNT)
constexpr int PIN_ENC_B        = 16;  // P1-9  shaft encoder channel B (PCNT)
constexpr int PIN_SPARE_UART_TX = 17; // P1-10 spare (UART1 TX, alt. Pi link)
constexpr int PIN_SPARE_UART_RX = 18; // P1-11 spare (UART1 RX, alt. Pi link)
// Free: 10 (P1-16), 11 (P1-17), 12 (P1-18), 13 (P1-19), 14 (P1-20)

// ---- USB-C ports ----
// Left  "USB": native USB (GPIO19/20) -> planned regulated power input only
// Right "COM": CH343 -> UART0 (GPIO43/44) -> flashing + host link (laptop now, Pi later)
// ESP32 powers no peripherals; sensors use a separate regulated rail, common ground.

// ---- Do not use ----
// GPIO3  (P1-13): strapping pin (JTAG signal source)
// GPIO46 (P1-14): strapping pin (boot mode / ROM log)
// GPIO35-37: wired to octal PSRAM inside the module (right header)
// GPIO19/20: native USB D-/D+ (right header); GPIO43/44: UART0 -> CH343 "COM" port
